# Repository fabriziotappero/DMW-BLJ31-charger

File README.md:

## Dual DMW-BLJ31 Charger
USB charger for the lithium battery DMW-BLJ31 capable of charging two batteries at the same time. 

This charger works with any USB 5V power adapter. One battery is charged at 5W and the other at 10W.

Traditional DMW-BLJ31 batteries are about 7.2V 25Wh that means that one charger is charging at approximately 0.5C and the other at 0.25C.

The charging time is approximately 2h and 4h, striking a reasonable balange between battery life and speed of charging.

## PCB 

## Pogo Pins
The length of the pogo pins (pring loaded pins) used here must be <2.5mm when compressed. Here are the pogo pins, available on [Amazon](https://www.amazon.es/dp/B0BXDG8MPN?th=1), that we recommend.

## DMW-BLJ31 Battery Dimensions

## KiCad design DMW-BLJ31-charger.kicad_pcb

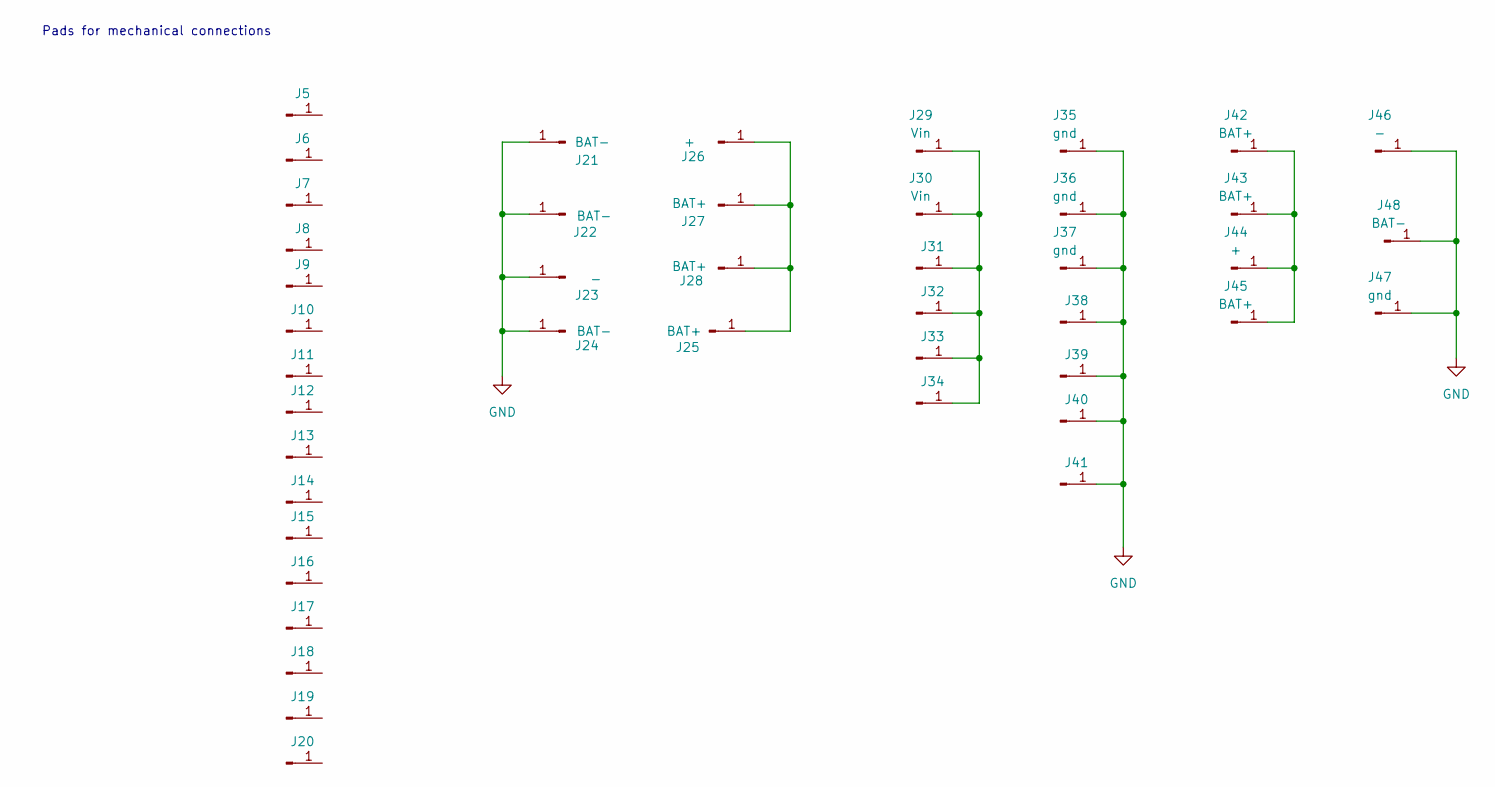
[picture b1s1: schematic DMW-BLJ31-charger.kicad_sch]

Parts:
J5, J6, J7, J8, J9, J10, J11, J12, J13, J14, J15, J16, J17, J18, J19, J20, J31, J32, J33, J34, J38, J39, J40, J41: SolderWire-0.25sqmm_1x01_D0.65mm_OD1.7mm
J21, J22, J24, J48: BAT-; SolderWire-0.25sqmm_1x01_D0.65mm_OD1.7mm
J23, J46: -; SolderWire-0.25sqmm_1x01_D0.65mm_OD1.7mm
J25, J27, J28, J42, J43, J45: BAT+; SolderWire-0.25sqmm_1x01_D0.65mm_OD1.7mm
J26, J44: +; SolderWire-0.25sqmm_1x01_D0.65mm_OD1.7mm
J29, J30: Vin; SolderWire-0.25sqmm_1x01_D0.65mm_OD1.7mm
J35, J36, J37, J47: gnd; SolderWire-0.25sqmm_1x01_D0.65mm_OD1.7mm

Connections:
GND: J21.1, J22.1, J23.1, J24.1, J35.1, J36.1, J37.1, J38.1, J39.1, J40.1, J41.1, J46.1, J47.1, J48.1
unnamed: J25.1, J26.1, J27.1, J28.1
unnamed: J29.1, J30.1, J31.1, J32.1, J33.1, J34.1
unnamed: J42.1, J43.1, J44.1, J45.1

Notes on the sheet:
Pads for mechanical connections

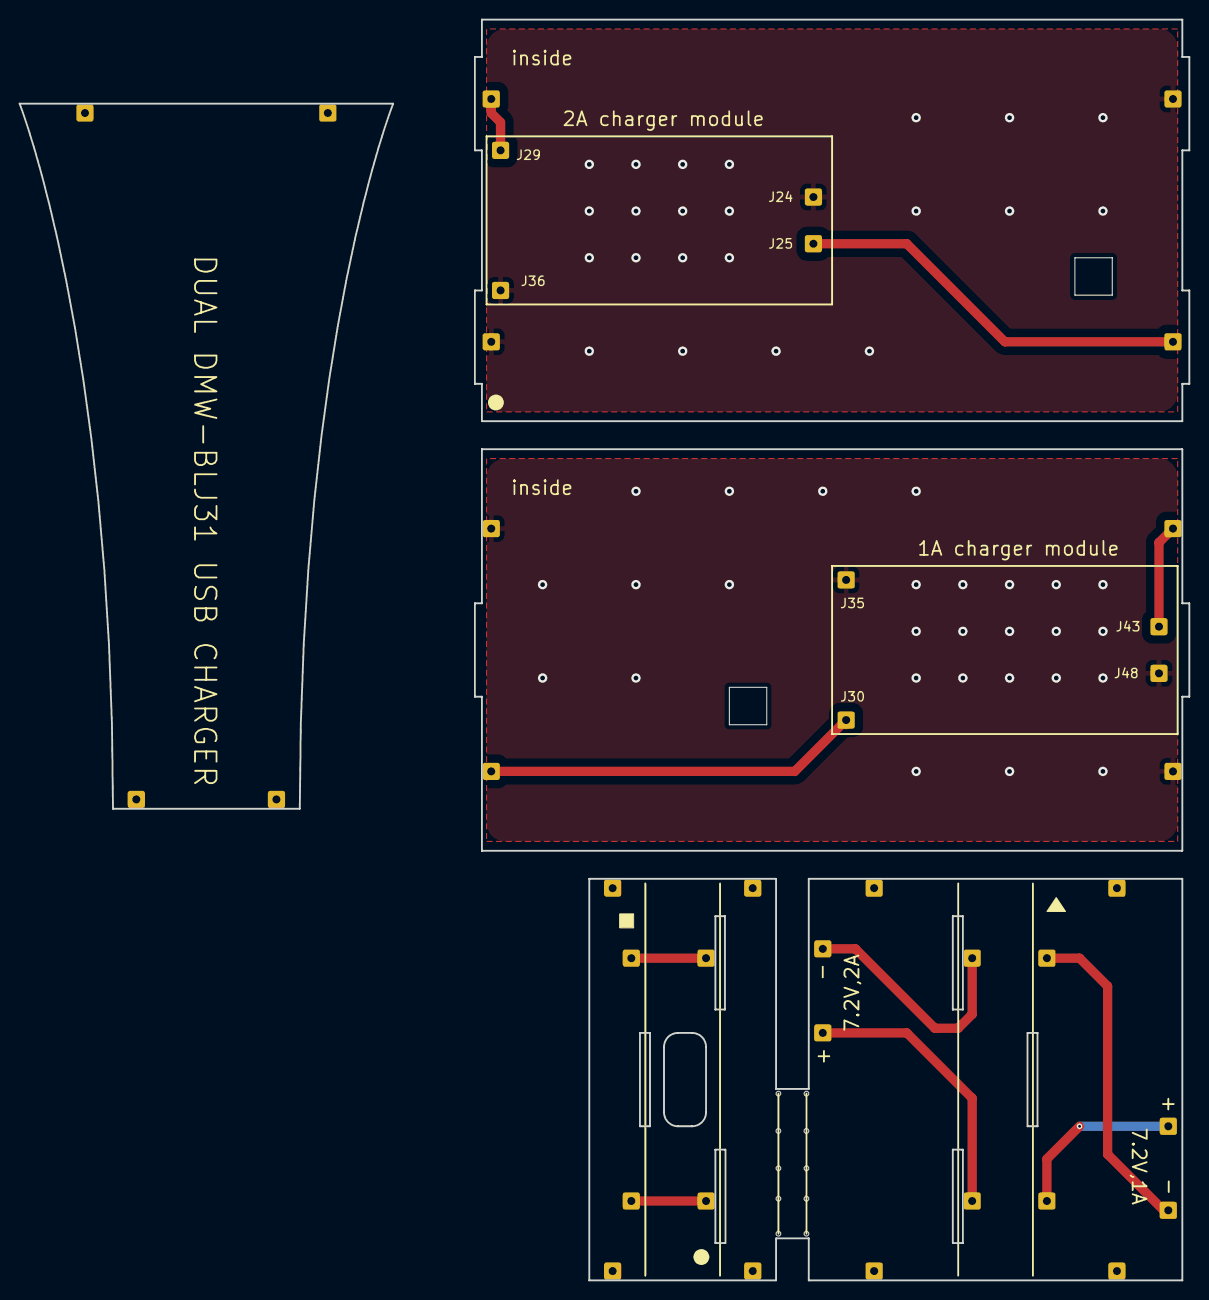
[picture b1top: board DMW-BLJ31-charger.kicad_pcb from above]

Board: 2 copper layers, 125.2 x 135.0 mm, 40 parts (0 on the bottom side), 4 nets.

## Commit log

2025-03-19 virst version
2025-03-20 refined case pads
2025-03-21 add battery data
2025-03-21 minor
2025-03-21 fix image link
2025-03-21 add description
2025-03-21 move charger module to different side
2025-03-21 update doc
2025-03-21 release version 1.2 with better mechanical mount
2025-03-21 better doc
2025-03-21 redesign layout to minimize fabrication costs
2025-03-22 move libs to lib folder
2025-03-23 change vias
